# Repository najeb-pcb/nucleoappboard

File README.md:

# STM32 Nucleo Application Board

A custom STM32 **Nucleo-compatible application board** designed for education, rapid prototyping, and embedded systems experimentation.

---

## 📌 Project Overview

The **STM32 Nucleo Application Board** is developed to:
- Support hands-on learning for STM32 microcontrollers
- Serve as a reusable application board across multiple STM32 Nucleo variants
- Provide a stable hardware platform for embedded firmware development and testing

The design is created using **KiCad** and follows good hardware documentation and version control practices.

---

## 🔧 Key Features

- STM32 **Nucleo header compatible**
- Designed for **educational and prototyping** use
- Breakout access to essential MCU peripherals
- Suitable for:
  - GPIO, ADC, PWM experiments
  - UART, I²C, SPI communication exercises
  - Embedded systems and microcontroller coursework
  - Rapid firmware and hardware validation

> Exact peripherals and features depend on the current schematic revision.

---

## 📁 Repository Structure

```
.
├── STM32AppBoard.kicad_sch   # Schematic design
├── STM32AppBoard.kicad_pcb   # PCB layout
├── STM32AppBoard.kicad_pro   # KiCad project file
├── .gitignore
└── README.md
```

KiCad auto-backups, cache files, and local configuration files are intentionally excluded from version control.

---

## 🛠️ Design Tools

- **EDA Software:** KiCad (version 6 or later recommended)
- **Target MCU Platform:** STM32 Nucleo series
- **Operating Systems Tested:** macOS, Linux

---

## 🚧 Project Status

- **Schematic:** In progress (iterative refinement)
- **PCB Layout:** In progress
- **Fabrication:** Not yet released
- **Firmware:** Not included in this repository

---

## 🔄 Versioning Strategy

- PCB and schematic revisions will follow tagged releases (e.g. `v1.0-pcb`)
- Only fabrication-relevant files will be included in releases
- Backup ZIP files are excluded to keep the repository clean

---

## 📦 Planned Additions

- PCB renders and schematic PDFs
- Fabrication-ready Gerber files
- Bill of Materials (BOM)
- Example firmware projects
- Hardware usage notes for teaching and labs

---

## 👤 Author

**Mohd Najeb Bin Jamaludin**  
Embedded Systems • Electronics • Education & Prototyping

---

## 📜 License

License to be defined.  
Until specified, this project is shared for **educational and non-commercial reference**.

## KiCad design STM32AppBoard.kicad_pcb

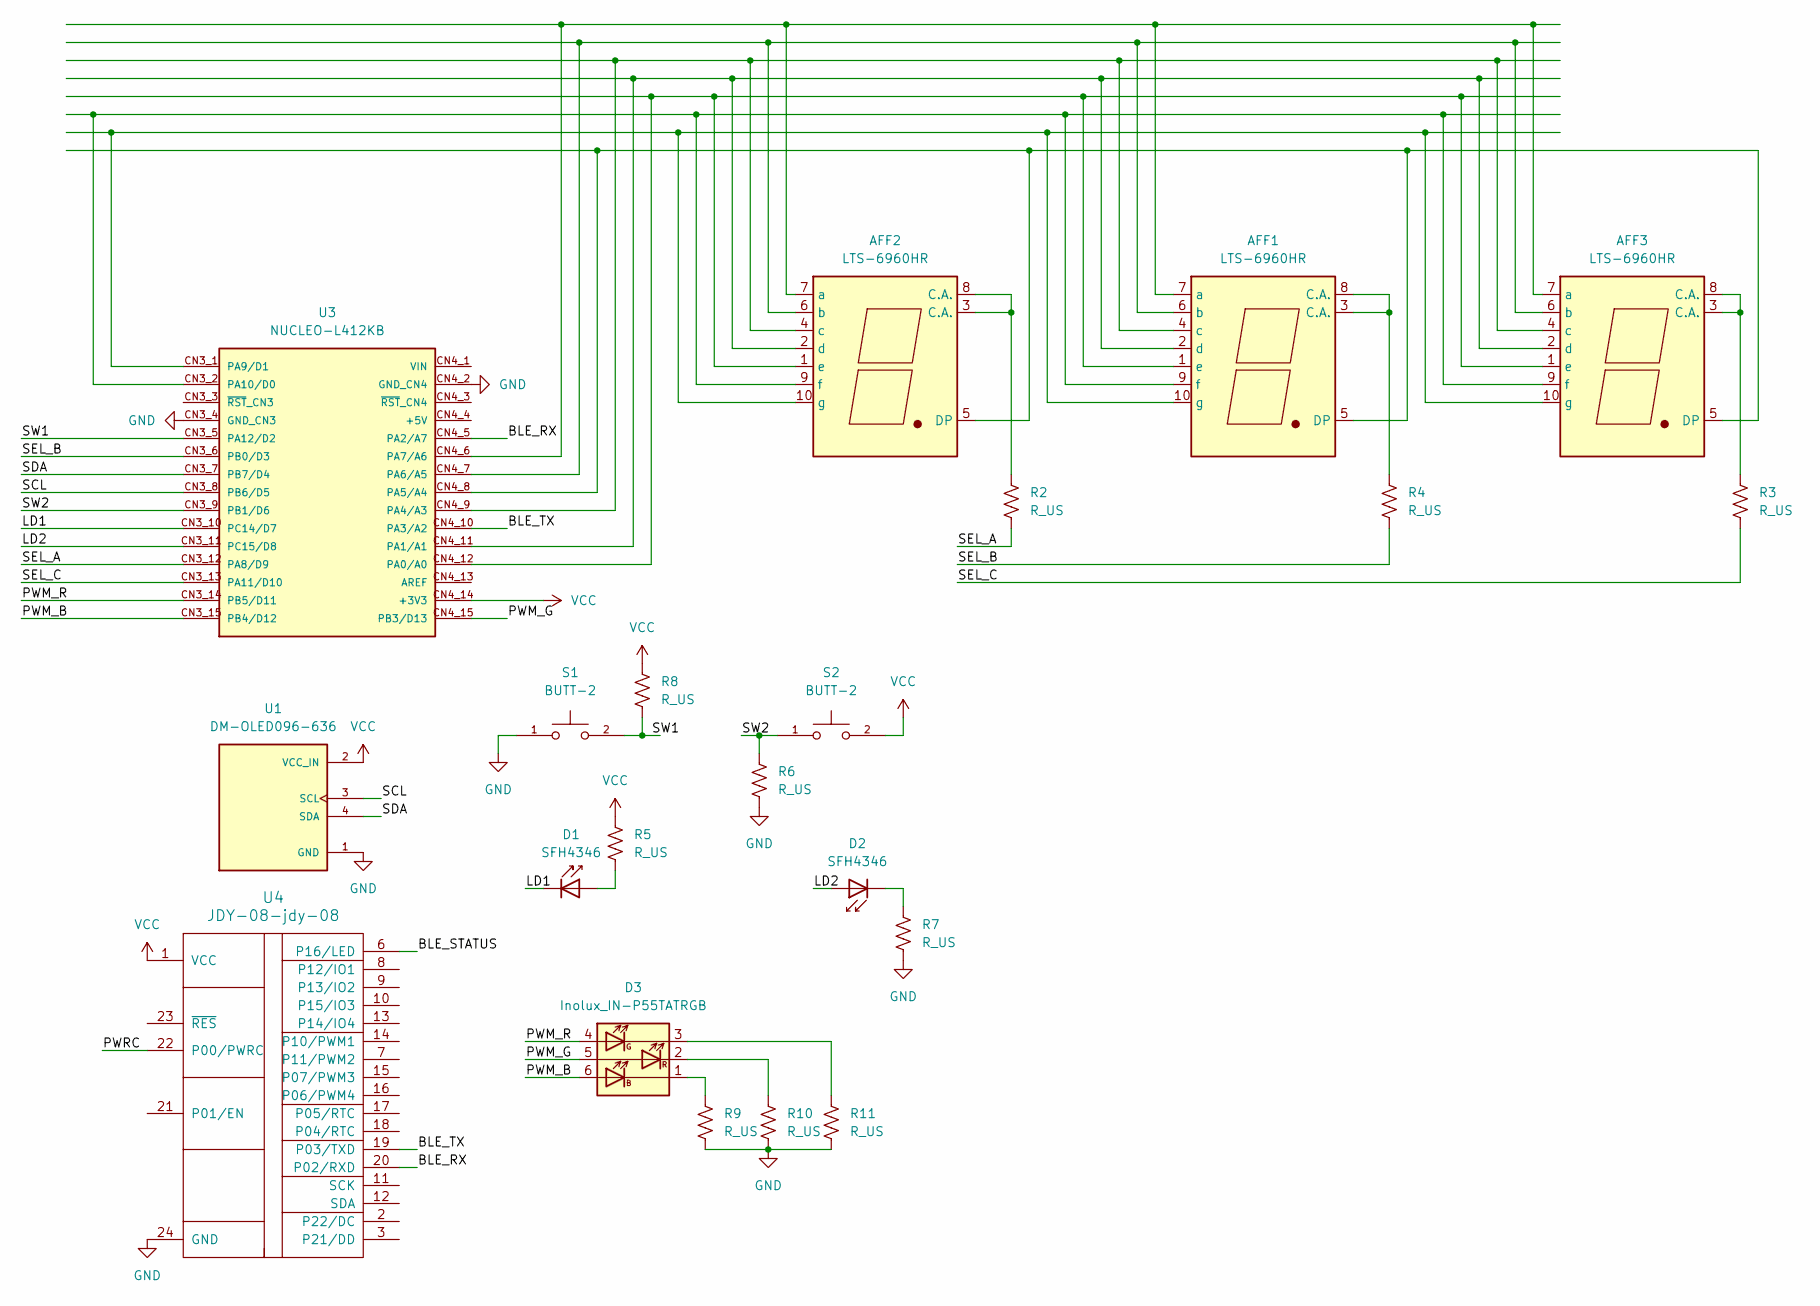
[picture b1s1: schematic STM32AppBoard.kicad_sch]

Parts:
AFF1, AFF2, AFF3: LTS-6960HR; 7SegmentLED_LTS6760_LTS6780
D1, D2: SFH4346; LED_D3.0mm_IRBlack
D3: Inolux_IN-P55TATRGB; LED_Inolux_IN-P55TATRGB_PLCC6_5.0x5.5mm_P1.8mm
R2, R3, R4, R5, R6, R7, R8, R9, R10, R11: R_US; R_Axial_DIN0207_L6.3mm_D2.5mm_P10.16mm_Horizontal
S1, S2: BUTT-2; SW_BUTT-2; PARTREV N/A
U1: DM-OLED096-636; MODULE_DM-OLED096-636; PARTREV 2018-09-10
U3: NUCLEO-L412KB; MODULE_NUCLEO-L412KB; PARTREV 8
U4: JDY-08-jdy-08; JDY-08_HandSoldering

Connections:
/BLE_RX: U3.CN4_5 (PA2/A7), U4.20 (P02/RXD)
/BLE_STATUS: U4.6 (P16/LED)
/BLE_TX: U3.CN4_10 (PA3/A2), U4.19 (P03/TXD)
/LD1: D1.1 (K), U3.CN3_10 (PC14/D7)
/LD2: D2.2 (A), U3.CN3_11 (PC15/D8)
/PWM_B: D3.6 (AB), U3.CN3_15 (PB4/D12)
/PWM_G: D3.5 (AR), U3.CN4_15 (PB3/D13)
/PWM_R: D3.4 (AG), U3.CN3_14 (PB5/D11)
/PWRC: U4.22 (P00/PWRC)
/SCL: U1.3 (SCL), U3.CN3_8 (PB6/D5)
/SDA: U1.4 (SDA), U3.CN3_7 (PB7/D4)
/SEL_A: R2.2, U3.CN3_12 (PA8/D9)
/SEL_B: R4.2, U3.CN3_6 (PB0/D3)
/SEL_C: R3.2, U3.CN3_13 (PA11/D10)
/SW1: R8.2, S1.2, U3.CN3_5 (PA12/D2)
/SW2: R6.1, S2.1, U3.CN3_9 (PB1/D6)
GND: R6.2, R7.2, R9.2, R10.2, R11.2, S1.1, U1.1 (GND), U3.CN3_4 (GND_CN3), U3.CN4_2 (GND_CN4), U4.24 (GND)
unnamed: AFF1.3 (C.A.), AFF1.8 (C.A.), R4.1
unnamed: AFF1.5 (DP), AFF2.5 (DP), AFF3.5 (DP), U3.CN4_8 (PA5/A4)
unnamed: AFF1.7 (a), AFF2.7 (a), AFF3.7 (a), U3.CN4_6 (PA7/A6)
unnamed: AFF1.6 (b), AFF2.6 (b), AFF3.6 (b), U3.CN4_7 (PA6/A5)
unnamed: AFF1.4 (c), AFF2.4 (c), AFF3.4 (c), U3.CN4_9 (PA4/A3)
unnamed: AFF1.2 (d), AFF2.2 (d), AFF3.2 (d), U3.CN4_11 (PA1/A1)
unnamed: AFF1.1 (e), AFF2.1 (e), AFF3.1 (e), U3.CN4_12 (PA0/A0)
unnamed: AFF1.9 (f), AFF2.9 (f), AFF3.9 (f), U3.CN3_2 (PA10/D0)
unnamed: AFF1.10 (g), AFF2.10 (g), AFF3.10 (g), U3.CN3_1 (PA9/D1)
unnamed: AFF2.3 (C.A.), AFF2.8 (C.A.), R2.1
unnamed: AFF3.3 (C.A.), AFF3.8 (C.A.), R3.1
unnamed: D1.2 (A), R5.2
unnamed: D2.1 (K), R7.1
unnamed: D3.1 (KB), R9.1
unnamed: D3.3 (KG), R11.1
unnamed: D3.2 (KR), R10.1
VCC: R5.1, R8.1, S2.2, U1.2 (VCC_IN), U3.CN4_14 (+3V3), U4.1 (VCC)

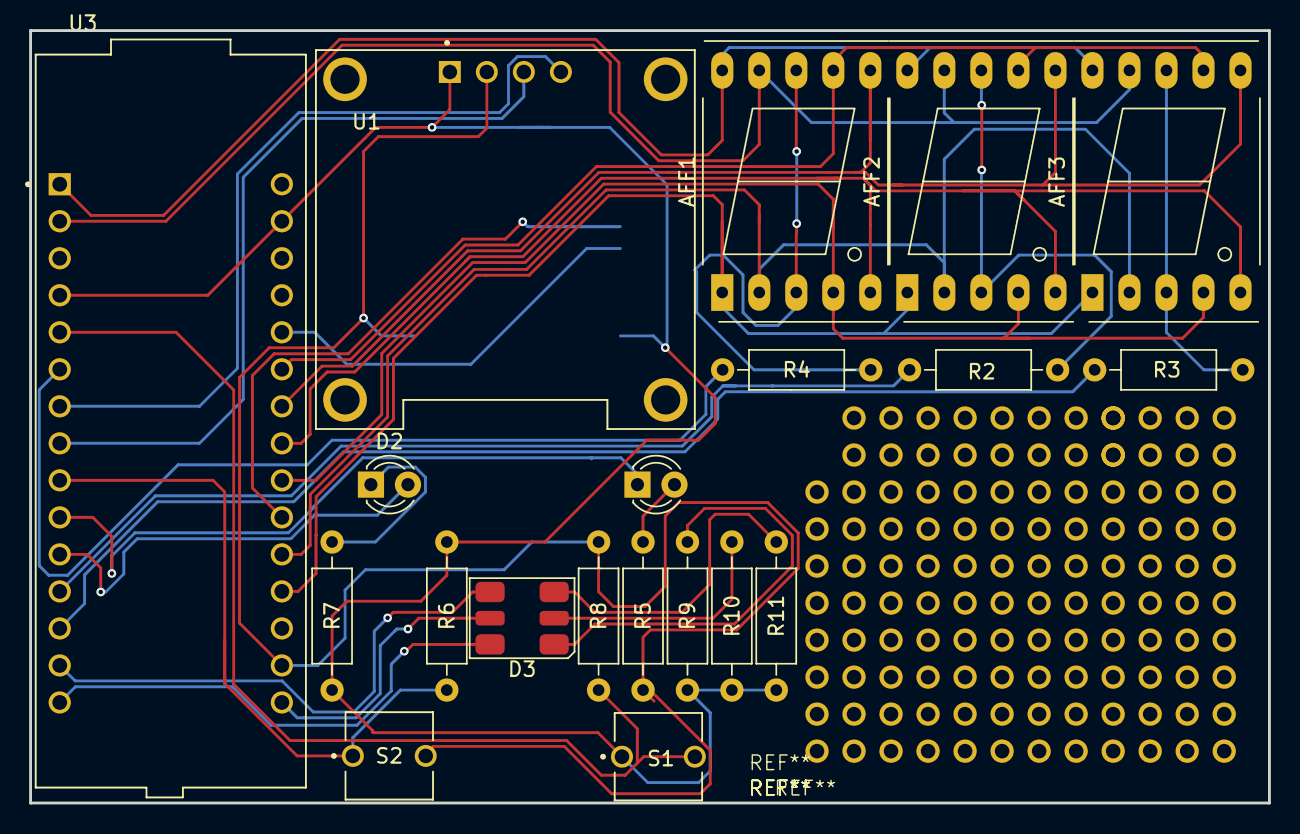
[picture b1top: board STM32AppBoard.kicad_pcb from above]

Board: 2 copper layers, 85.0 x 53.0 mm, 21 parts (1 on the bottom side), 32 nets.

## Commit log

2025-12-09 Initial KiCad project commit
2025-12-09 Initial commit of STM32 App Board KiCad files
2025-12-16 Update STM32AppBoard schematic and PCB layout
2025-12-16 Add project README
2025-12-16 Add 3D PCB render
2025-12-16 Update README with board overview image
2025-12-16 Update PCB 3D render image
2025-12-16 Remove KiCad backups folder from repository
